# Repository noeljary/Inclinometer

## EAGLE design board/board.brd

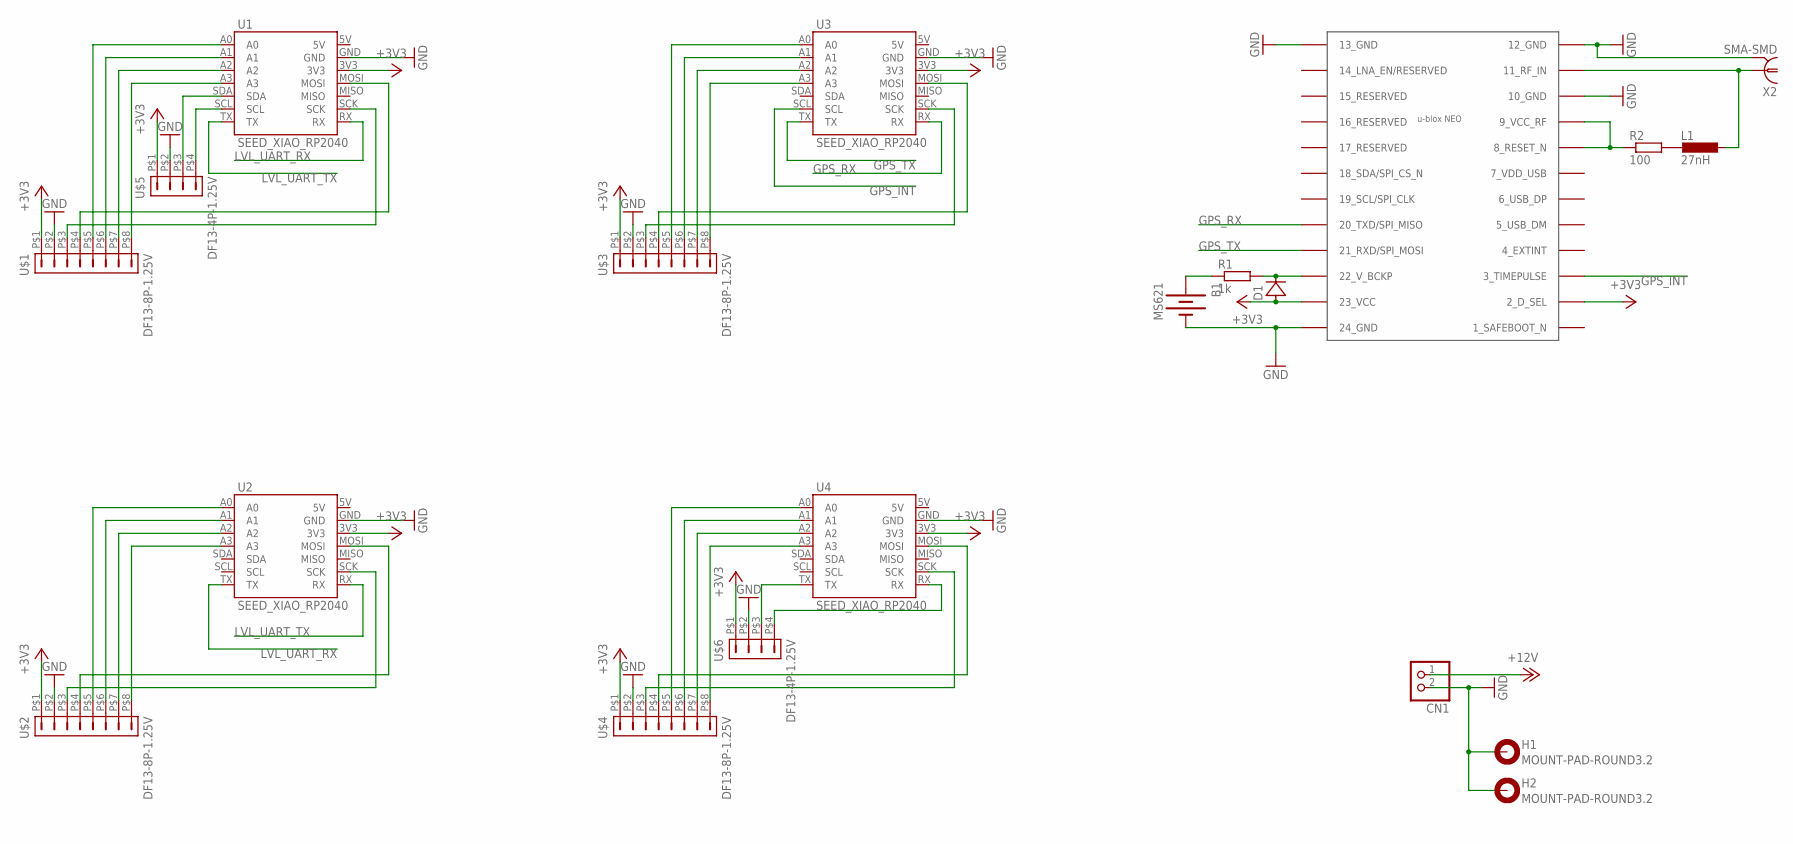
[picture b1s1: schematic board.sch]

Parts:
B1: MS621; MS621FE-IL36E
CN1: JST_2PIN-SMT-RA; JST-PH-2-SMT-RA
D1: DIODESOD-123; SOD123
H1, H2: MOUNT-PAD-ROUND3.2; 3,2-PAD
L1: 27nH; L2012C
R1: 1k; R0805
R2: 100; R0805
U1, U2, U3, U4: SEED_XIAO_RP2040
U$1, U$2, U$3, U$4: DF13-8P-1.25V; DF13C-8P-1.25V
U$5, U$6: DF13-4P-1.25V; DF13C-4P-1.25V
U$7: NEO-M8
X2: SMA-SMD

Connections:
+3V3: D1.A, U1.3V3, U2.3V3, U3.3V3, U4.3V3, U$1.P$1 (1), U$2.P$1 (1), U$3.P$1 (1), U$4.P$1 (1), U$5.P$1 (1), U$6.P$1 (1), U$7.2 (2_D_SEL), U$7.23 (23_VCC)
+12V: CN1.1 (2)
GND: B1.P$1 (-), CN1.2 (1), H1.B3,2, H1.P$1, H1.P$2, H1.P$3, H1.P$4, H1.P$5, H1.P$6, H1.P$7, H1.P$8, H2.B3,2, H2.P$1, H2.P$2, H2.P$3, H2.P$4, H2.P$5, H2.P$6, H2.P$7, H2.P$8, U1.GND, U2.GND, U3.GND, U4.GND, U$1.P$2 (2), U$2.P$2 (2), U$3.P$2 (2), U$4.P$2 (2), U$5.P$2 (2), U$6.P$2 (2), U$7.10 (10_GND), U$7.12 (12_GND), U$7.13 (13_GND), U$7.24 (24_GND), X2.2@1 (2), X2.2@2 (2), X2.2@3 (2), X2.2@4 (2), X2.2@5 (2), X2.2@6 (2)
GPS_INT: U3.SCL, U$7.3 (3_TIMEPULSE)
GPS_RX: U3.RX, U$7.20 (20_TXD/SPI_MISO)
GPS_TX: U3.TX, U$7.21 (21_RXD/SPI_MOSI)
LVL_UART_RX: U1.RX, U2.TX
LVL_UART_TX: U1.TX, U2.RX
unnamed: U1.A3, U$1.P$8 (8)
unnamed: U1.A2, U$1.P$7 (7)
unnamed: U1.SCL, U$5.P$4 (4)
unnamed: U1.SDA, U$5.P$3 (3)
unnamed: U1.A1, U$1.P$6 (6)
unnamed: U1.A0, U$1.P$5 (5)
unnamed: U1.SCK, U$1.P$3 (3)
unnamed: U1.MOSI, U$1.P$4 (4)
unnamed: U2.SCK, U$2.P$3 (3)
unnamed: U2.MOSI, U$2.P$4 (4)
unnamed: U2.A3, U$2.P$8 (8)
unnamed: U2.A2, U$2.P$7 (7)
unnamed: U2.A1, U$2.P$6 (6)
unnamed: U2.A0, U$2.P$5 (5)
unnamed: U3.A3, U$3.P$8 (8)
unnamed: U3.A2, U$3.P$7 (7)
unnamed: U3.A1, U$3.P$6 (6)
unnamed: U3.A0, U$3.P$5 (5)
unnamed: U3.SCK, U$3.P$3 (3)
unnamed: U3.MOSI, U$3.P$4 (4)
unnamed: U4.A3, U$4.P$8 (8)
unnamed: U4.A2, U$4.P$7 (7)
unnamed: U4.A1, U$4.P$6 (6)
unnamed: U4.A0, U$4.P$5 (5)
unnamed: U4.SCK, U$4.P$3 (3)
unnamed: U4.MOSI, U$4.P$4 (4)
unnamed: U4.TX, U$6.P$3 (3)
unnamed: U4.RX, U$6.P$4 (4)
unnamed: L1.1, U$7.11 (11_RF_IN), X2.1
unnamed: B1.P$2 (+), R1.1
unnamed: D1.C, R1.2, U$7.22 (22_V_BCKP)
unnamed: R2.1, U$7.8 (8_RESET_N), U$7.9 (9_VCC_RF)
unnamed: L1.2, R2.2

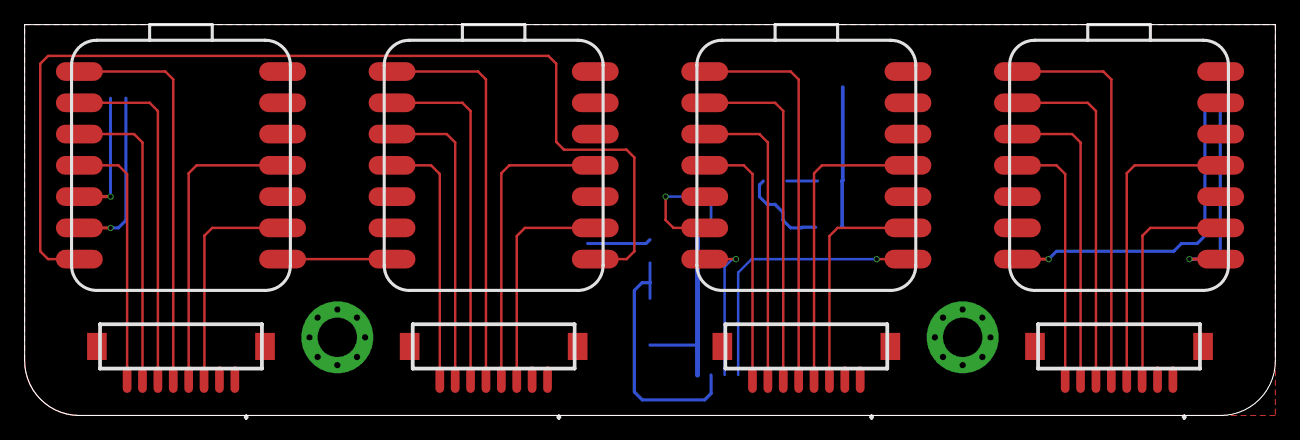
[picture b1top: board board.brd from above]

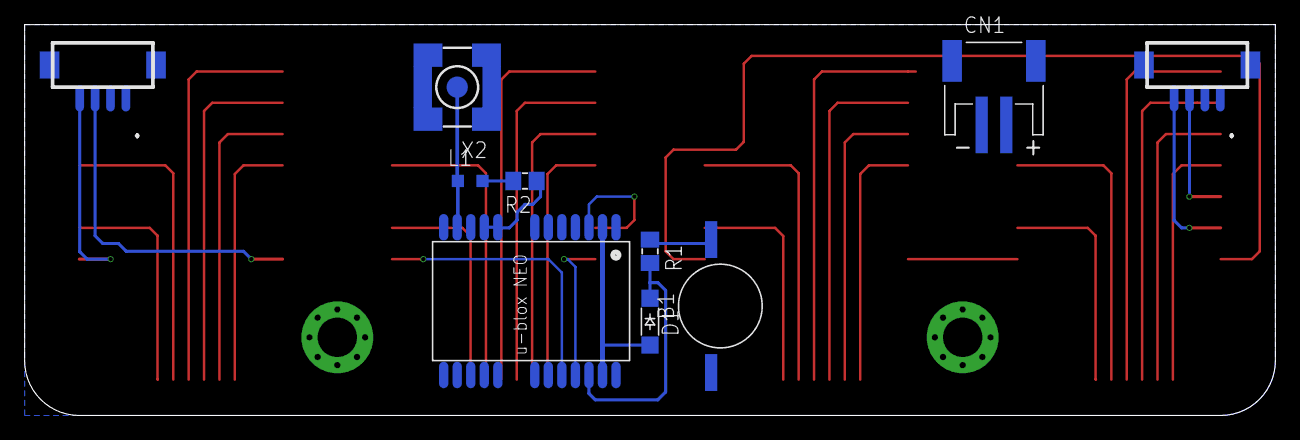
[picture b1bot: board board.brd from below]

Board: 2 copper layers, 101.6 x 31.8 mm, 20 parts (10 on the bottom side), 40 nets.

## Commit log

2021-07-15 Initial commit of basic compass/pitch/roll to serial output
2022-12-02 Post POC commit with modularised components
2022-12-03 Add circuit schematics and board
2022-12-23 Sort bug where lat/lng show negative despite having relevant cardinal
2022-12-23 Update vertical element alignment
2022-12-23 Fix introduced tab whitespace
2023-11-25 Migrated board design into KiCAD7 from EAGLE. v1.0 of manufactured board including gerber files
2023-11-25 Rewritten TPMS Display in Micropythin for vastly superior performance
2023-11-25 Mock tool for TPMS system - sends data to TPMS Display as if it had received it wirelessly for testing purposes
2023-11-25 Attaching micropython binary compiled for RP2040, including C driver for GC9A01 and updated framebuffer with bitmap image and font support
2023-11-25 Adding initial revision of GPS module code in micropython. Needs refactoring to same framework level as TPMS Display
2023-11-25 First revision of TPMS Wirelss Receiver code. Refactored version of JSMSolns 'Arduino TPMS Tyre Pressure Display' - removed all display logic, and unnecessary parts, initially only supports Toyota PM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
2023-11-25 Refactored to TPMS Display Standard. Series of GPS Parsing Library bug fixes.
2023-11-26 Added units management to GPS screens with file saving for persistance
2023-11-26 Fix what seems to be a find/replace issue in TPMS code but no idea how it got there
2023-11-27 Added blueprint for Timezone management
